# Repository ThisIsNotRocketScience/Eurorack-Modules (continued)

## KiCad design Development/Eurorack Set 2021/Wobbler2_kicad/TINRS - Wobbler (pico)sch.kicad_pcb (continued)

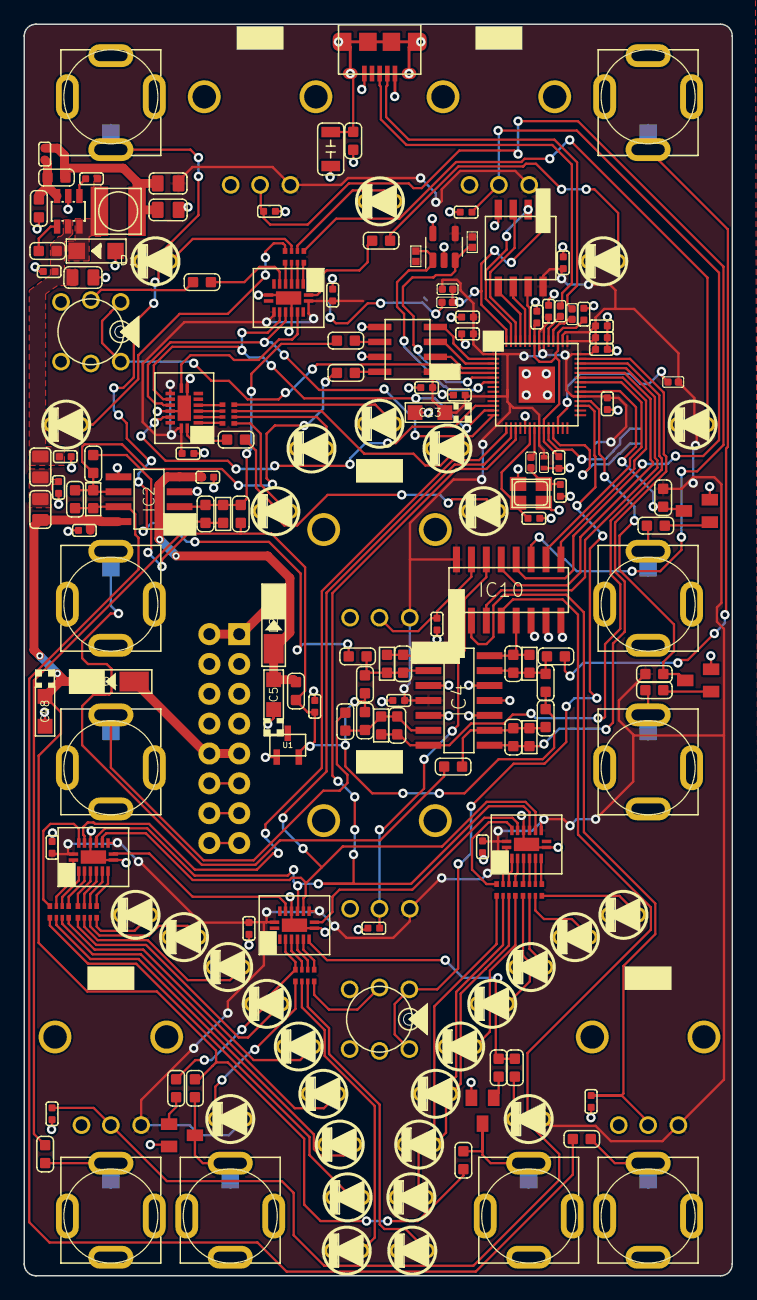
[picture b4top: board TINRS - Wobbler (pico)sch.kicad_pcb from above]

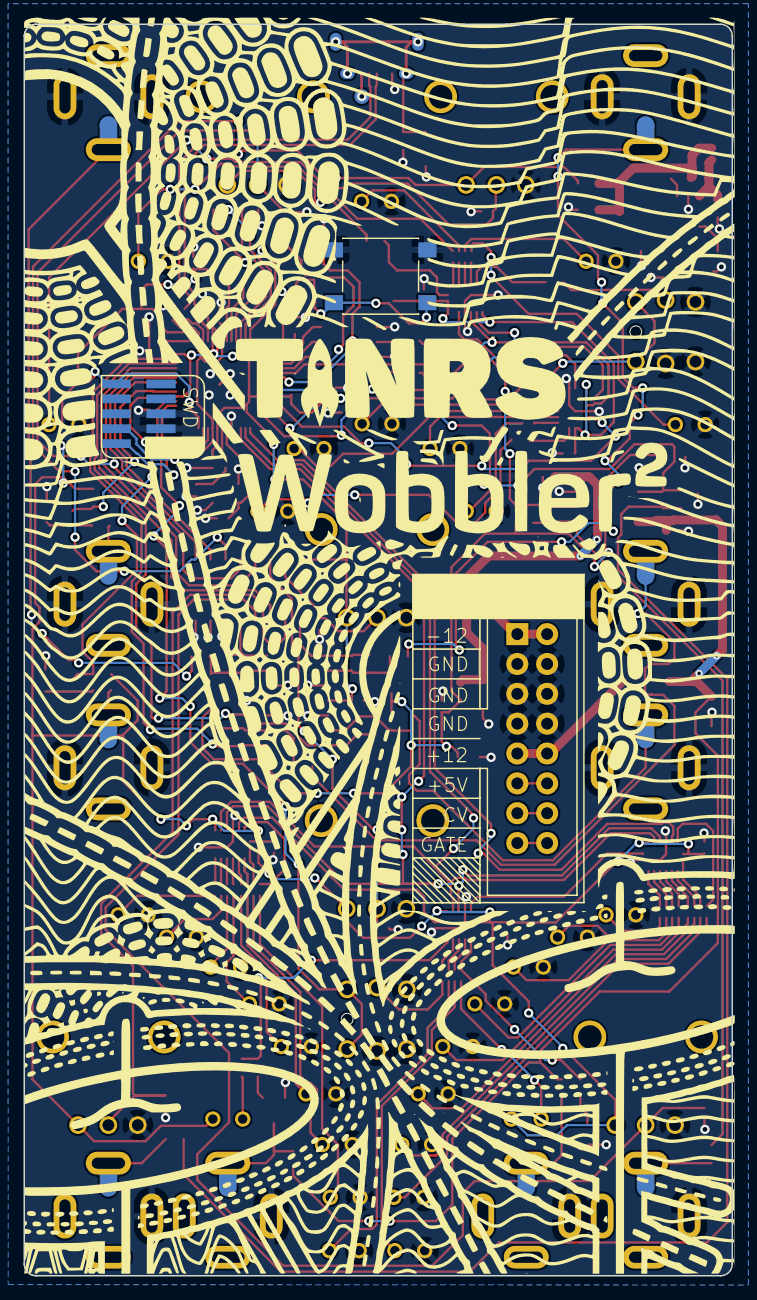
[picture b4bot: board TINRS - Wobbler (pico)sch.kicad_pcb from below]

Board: 2 copper layers, 60.3 x 106.5 mm, 181 parts (5 on the bottom side), 157 nets.

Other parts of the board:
A1: Wobbler2_PCBArt; Wobbler2_art
R35, R38: 2k; R0402
U2: AT24CS01-STUM; SOT-23-5

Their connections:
/MCU & Eeprom/EEPROM_SCL: R38.2, U2.1 (SCL); also elsewhere on the board
/MCU & Eeprom/EEPROM_SDA: R35.1, U2.3 (SDA); also elsewhere on the board
GND: U2.2 (GND), U2.5 (WP); also elsewhere on the board

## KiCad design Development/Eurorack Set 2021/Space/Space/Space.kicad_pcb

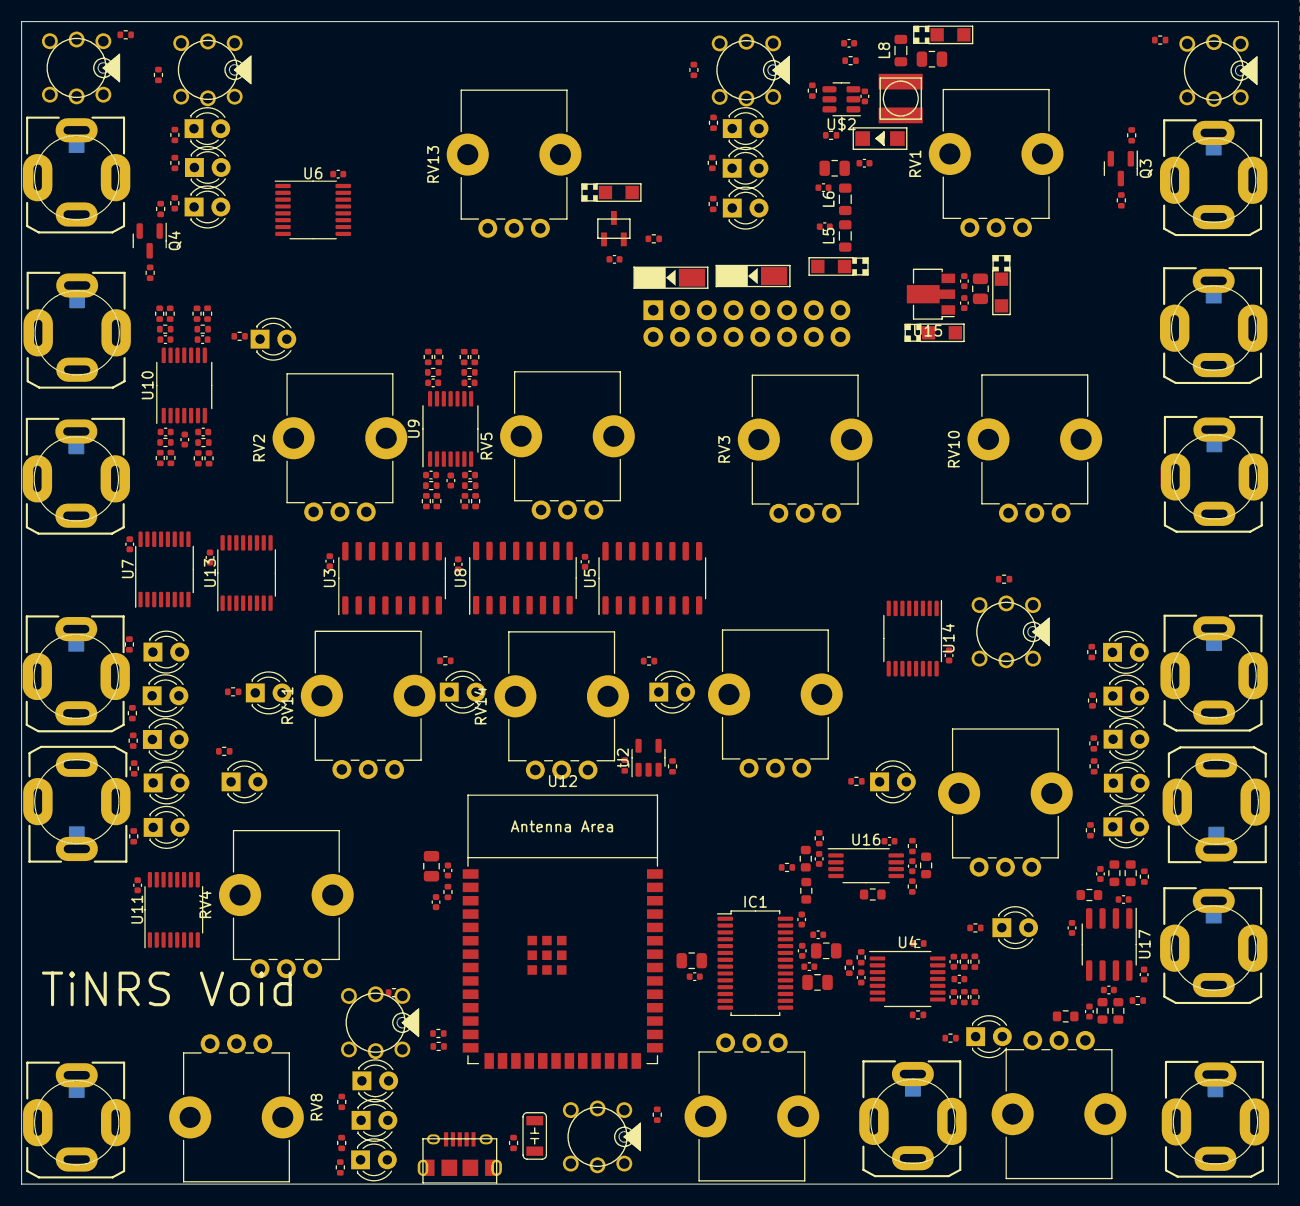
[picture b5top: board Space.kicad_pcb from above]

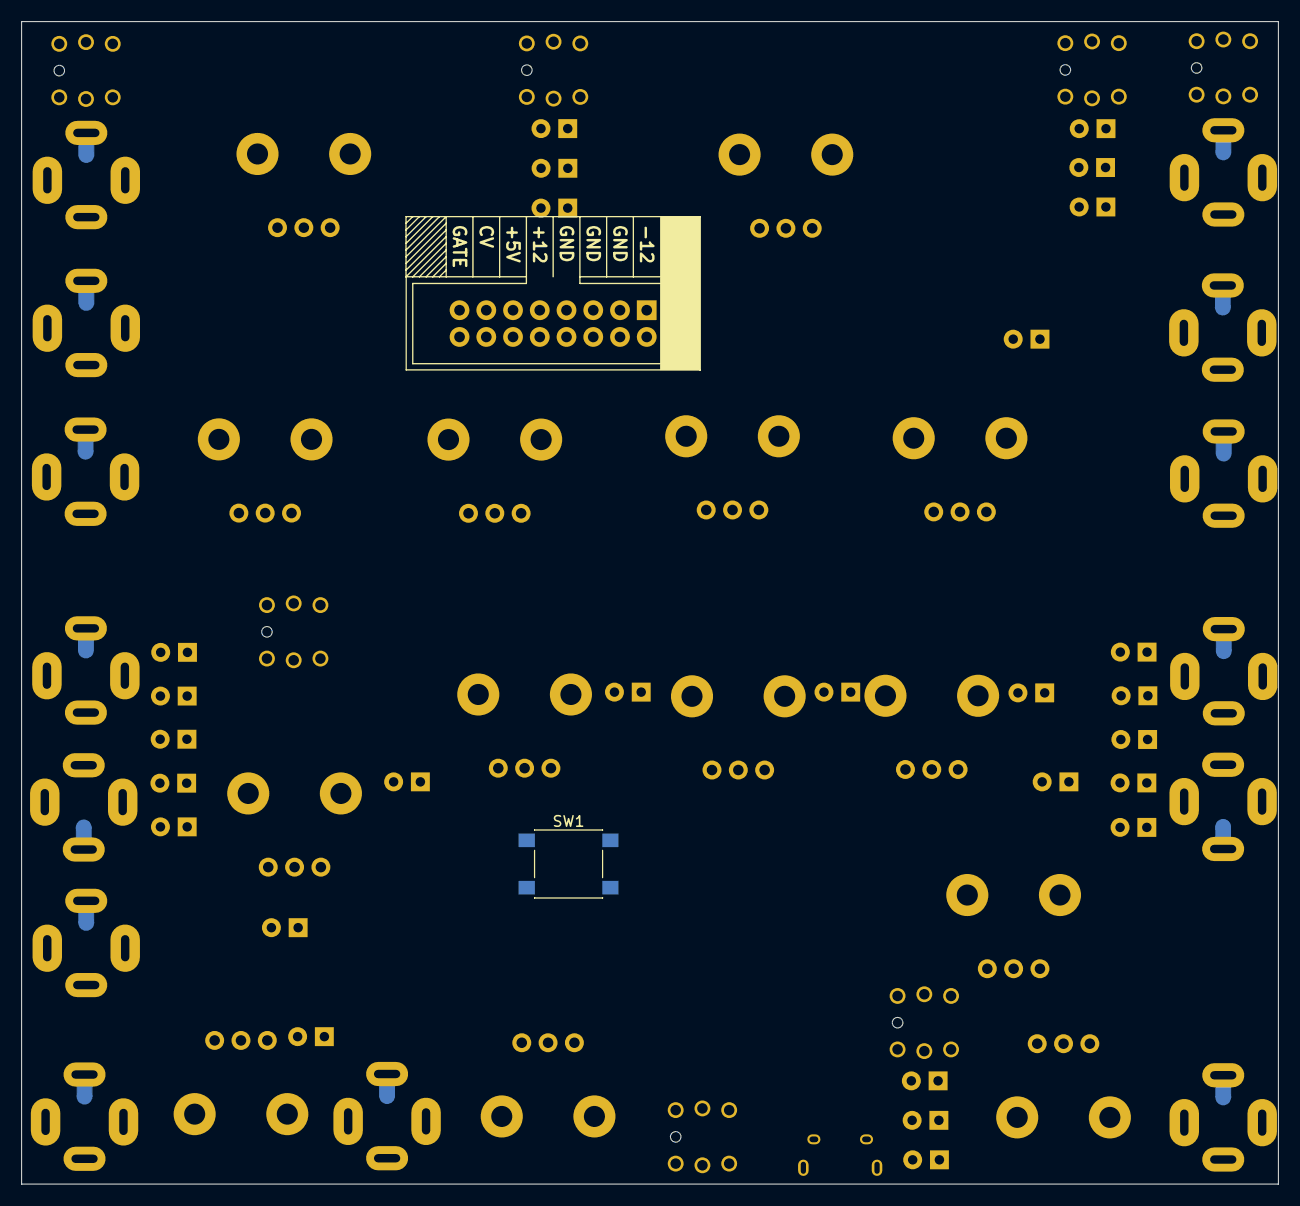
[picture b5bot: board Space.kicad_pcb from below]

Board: 2 copper layers, 119.4 x 110.4 mm, 248 parts (2 on the bottom side), 189 nets, no tracks yet.

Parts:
C1, C2, C48, C51, C52, C53, C56: 1759017; C_0402_1005Metric
C3, C8, C50, C55, C58: 197427; CASE-A_3216
C7, C54, C61: 22u; C_0805_2012Metric
C9, C12, C15: 10u; C_0805_2012Metric
C10, C13, C16, C26, C27, C28, C29, C31, C32, C33, C34, C35, C36, C45, C46, C47, C62, C63, C64: 100n; C_0402_1005Metric
C11, C14: 2.2n; C_0402_1005Metric
C24, C25: 470p; C_0402_1005Metric
C37, C38, C39, C40, C41, C42, C43, C44: 3.3n; C_0402_1005Metric
C49: 10uF; C_0805_2012Metric
C57: 1301804; C_0402_1005Metric
C59: 4.7n 100v; C3216
C60: 1u; C_0402_1005Metric
C65, C66: 100p; C_0402_1005Metric
C67, C68, C69, C70: 47p; C_0402_1005Metric
D1, D4, D7, D8, D9, D10, D11, D12, D13, D14, D15, D16, D17, D18, D19, D20, D23, D24, D25, D26, D27, D28, D29, D30, D31, D32, D33: LED; LED_D3.0mm_FlatTop
D3: D-SOD-123; SOD123
D21, D22: D-SMA; DO-214AC
IC1: PCM3060; TSSOP-28_4.4x9.7mm_P0.65mm
J1: unknown; POWER_16_SHROUDED
J14: MICRO-USB-5P; C132563
JACK1, JACK2, JACK3, JACK4, JACK5, JACK6, JACK7, JACK8, JACK9, JACK10, JACK11, JACK12, JACK13, JACK14: AUDIO-JACK_SMALLSYMBOLNODRILL; 3.5MM-JACK-SWITCH-13MM-NOHOLES-TESTPAD
L5, L6, L8: 0.1uH C76737; L_0805_2012Metric
L7: 4.7uH; L0420
Q3, Q4: MMBT3904; SOT-23
R1, R2, R4, R25, R26, R27, R28, R29, R30, R31, R32, R33, R34, R35, R36, R37, R62, R63, R64, R65, R79, R80, R81, R82, R83, R84, R85, R86, R87, R88, R89, R90, R91, R92, R110, R115: 56; R_0402_1005Metric
R38, R39, R40, R41, R44, R45, R46, R47, R50, R51, R52, R53, R56, R57, R58, R59, R67, R99, R102, R103, R104, R105, R106, R114, R116, R117: 100k; R_0402_1005Metric
R42, R43, R48, R49, R54, R55, R60, R61: 33k; R_0402_1005Metric
R66, R68, R100, R101: 12.1k; R_0603_1608Metric
R69, R70, R71, R72, R93, R94, R95, R96: unknown; R_0402_1005Metric
R73, R74: 0; R_0402_1005Metric
R75: 1M; R_0402_1005Metric
R76, R77: 2k; R_0402_1005Metric
R78: 10k; R_0402_1005Metric
R97, R98: 100; R_0402_1005Metric
R107, R112: 4.42k; R_0603_1608Metric
R108, R113: 4.02k; R_0603_1608Metric
R109, R111: 37.5k; R_0603_1608Metric
RV1, RV2, RV3, RV4, RV5, RV6, RV8, RV9, RV10, RV11, RV13, RV14, RV15, RV16: R_Potentiometer; Potentiometer_Alps_RK09K_Single_Vertical
SW1: SW_Push; SW_Push_1P1T_NO_6x6mm_H9.5mm
U1: 9778330; SOT95P237X112-3N
U2: AT24CS01-STUM; SOT-23-5
U3, U5, U8: 4052; SO-16_3.9x9.9mm_P1.27mm
U4: TL074; TSSOP-14_4.4x5mm_P0.65mm
U6, U7, U11, U13, U14: 74HC595; TSSOP-16_4.4x5mm_P0.65mm
U9, U10: MCP6004; TSSOP-14_4.4x5mm_P0.65mm
U12: ESP32-S3-WROOM-1
U15: HT7550-1; SOT-89-3
U16: MCP6022; TSSOP-8_4.4x3mm_P0.65mm
U17: NE5532; SOIC-8_3.9x4.9mm_P1.27mm
U$2: BL9342; SOT-23-6
U$3, U$4, U$5, U$6, U$7, U$8, U$9: SWITCH_W_LED_PB6149L-X-102YELLOW; PB6149L

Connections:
+3V3: C9.1, C10.1, C31.1, C32.1, C33.1, C34.1, C35.1, C36.1, C45.2, C46.1, C55.+ (1), C61.1, C62.1, C63.1, C64.1, IC1.7 (VDD), L8.2, R76.2, R77.1, R78.1, R93.2, R95.2, RV1.3, RV2.3, RV3.3, RV4.3, RV5.3, RV6.3, RV8.3, RV9.3, RV10.3, RV11.3, RV13.3, RV14.3, RV15.3, RV16.3, U2.4 (VCC), U3.16 (VDD), U5.16 (VDD), U6.10 (~SRCLR), U6.16 (VCC), U7.10 (~SRCLR), U7.16 (VCC), U8.16 (VDD), U9.4 (V+), U10.4 (V+), U11.10 (~SRCLR), U11.16 (VCC), U12.2 (3V3), U13.10 (~SRCLR), U13.16 (VCC), U14.10 (~SRCLR), U14.16 (VCC)
+5V: C1.1, C7.2, C8.+ (1), C15.1, C16.1, C47.1, IC1.24 (VCC), U15.3 (OUT), U16.8 (V+)
+12V: C2.1, C3.+ (1), C27.1, C28.1, C50.+ (1), D21.2 (-), L5.1, U4.4 (V+), U15.2 (IN), U17.8 (V+)
-5V: C57.2, R38.1, R40.1, R44.1, R46.1, R50.1, R52.1, R56.1, R58.1, R72.2, U1.2 (ANODE)
-12V: C26.1, C29.1, C58.- (2), D22.1 (+), R72.1, U4.11 (V-), U17.4 (V-)
/BOOTSEL_BUT: SW1.2, U12.27 (GPIO0/BOOT)
/BUTTON_DELAY: U12.29 (SPIIO7/GPIO36/FSPICLK/SUBSPICLK), U$7.1, U$7.2
/BUTTON_FREEZE: U12.23 (GPIO21), U$4.1, U$4.2
/BUTTON_PITCH: U12.24 (GPIO47/SPICLK_P/SUBSPICLK_P_DIFF), U$8.1, U$8.2
/BUTTON_PITCHPOINT: U12.25 (GPIO48/SPICLK_N/SUBSPICLK_N_DIFF), U$5.1, U$5.2
/BUTTON_SEND: U12.16 (GPIO46), U$6.1, U$6.2
/BUTTON_TAIL: U12.26 (GPIO45), U$9.1, U$9.2
/BUTTON_TAP: U12.28 (SPIIO6/GPIO35/FSPID/SUBSPID), U$3.1, U$3.2
/CODEC_SCL: IC1.1 (MC/SCL/FMT), U12.15 (GPIO3/TOUCH3/ADC1_CH2)
/CODEC_SDA: IC1.2 (MD/SDA/DEMP), U12.38 (GPIO2/TOUCH2/ADC1_CH1)
/CVADC0: U8.13 (X), U12.19 (GPIO11/TOUCH11/ADC2_CH0/FSPID/FSPIIO5/S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)
/CVADC1: U8.3 (Y), U12.20 (GPIO12/TOUCH12/ADC2_CH1/FSPICLK/FSPIIO6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)
/CVJacks/CV_DELAY_FEEDBACK: JACK2.TIP, R41.1
/CVJacks/CV_DELAY_LENGTH: JACK1.TIP, R39.1
/CVJacks/CV_MIX: JACK7.TIP, R57.1
/CVJacks/CV_PITCH_CONTROL: JACK4.TIP, R47.1
/CVJacks/CV_PITCH_TRANSPOSE: JACK3.TIP, R45.1
/CVJacks/CV_TAIL_LENGTH: JACK6.TIP, R53.1
/CVJacks/CV_TAIL_TEMPERATURE: JACK5.TIP, R51.1
/CVJacks/JACK_FREEZE: JACK9.TIP, R96.1
/CVJacks/JACK_TAP: JACK10.TIP, R94.1
/CVJacks/XCV0: C38.2, R43.2, U8.12 (X0), U9.1
/CVJacks/XCV1: C40.2, R49.2, U8.14 (X1), U9.7
/CVJacks/XCV2: C42.2, R55.2, U8.15 (X2), U9.8
/CVJacks/XCV3: C44.2, R61.2, U8.11 (X3), U9.14
/CVJacks/XCV4: C37.2, R42.2, U8.1 (Y0), U10.1
/CVJacks/XCV5: C39.2, R48.2, U8.5 (Y1), U10.7
/CVJacks/XCV6: C41.2, R54.2, U8.2 (Y2), U10.8
/CVJacks/XCV7: C43.2, R60.2, U8.4 (Y3), U10.14
/CVMUX0: U3.10 (A), U5.10 (A), U8.10 (A), U12.30 (SPIDQS/GPIO37/FSPIQ/SUBSPIQ)
/CVMUX1: U3.9 (B), U5.9 (B), U8.9 (B), U12.31 (GPIO38/FSPIWP/SUBSPIWP)
/CodecBuffer/BIAS_BUFFERED: R102.1, U4.6 (-), U4.7
/CodecBuffer/BIAS_INVERTED: R68.1, R100.1, R103.2, R106.1, R117.1, U4.1
/CodecBuffer/In_Jack_Left: JACK13.TIP, JACK14.SWITCH, R67.1
/CodecBuffer/In_Jack_Right: JACK14.TIP, R99.1
/CodecBuffer/Out_Jack_Left: JACK11.TIP, R110.2
/CodecBuffer/Out_Jack_Right: JACK12.TIP, R115.2
/CodecBuffer/Out_Left: IC1.20 (VOUTL+), R114.1
/CodecBuffer/Out_Right: IC1.18 (VOUTR+), R105.1
/EEPROM_SCL: R77.2, U2.1 (SCL), U12.33 (MTDO/GPIO40/CLK_OUT2)
/EEPROM_SDA: R76.1, U2.3 (SDA), U12.32 (MTCK/GPIO39/CLK_OUT3/SUBSPICS1)
/EN: C60.1, R78.2, U12.3 (EN)
/I2S_BCLK: IC1.5 (BCK1), U12.11 (GPIO18/U1RXD/ADC2_CH7/CLK_OUT3)
/I2S_LRC: IC1.4 (LRCK1), U12.10 (GPIO17/U1TXD/ADC2_CH6)
/JACK_FREEZE: Q3.3 (C), R95.1, U12.39 (GPIO1/TOUCH1/ADC1_CH0)
/JACK_TAP: Q4.3 (C), R93.1, U12.34 (MTDI/GPIO41/CLK_OUT1)
/KNOBADC0: U3.13 (X), U12.7 (GPIO7/TOUCH7/ADC1_CH6)
/KNOBADC1: U3.3 (Y), U12.12 (GPIO8/TOUCH8/ADC1_CH7/SUBSPICS1)
/KNOBADC2: U5.13 (X), U12.17 (GPIO9/TOUCH9/ADC1_CH8/FSPIHD/SUBSPIHD)
/KNOBADC3: U5.3 (Y), U12.18 (GPIO10/TOUCH10/ADC1_CH9/FSPICS0/FSPIIO4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)
/Knobs/KNOB_DELAY: RV14.2, U3.1 (Y0)
/Knobs/KNOB_DELAY_FEEDBACK: RV2.2, U3.14 (X1)
/Knobs/KNOB_DELAY_LENGTH: RV13.2, U3.12 (X0)
/Knobs/KNOB_DELAY_PATTERN: RV5.2, U3.15 (X2)
/Knobs/KNOB_DIFFUSE: RV11.2, U3.11 (X3)
/Knobs/KNOB_DIFFUSE_STYLE: RV4.2, U3.5 (Y1)
/Knobs/KNOB_ENVTRACK: RV9.2, U5.5 (Y1)
/Knobs/KNOB_MAIN: RV15.2, U5.1 (Y0)
/Knobs/KNOB_PITCH_CONTROL: RV16.2, U5.2 (Y2)
/Knobs/KNOB_PITCH_TRANSPOSE: RV8.2, U3.2 (Y2)
/Knobs/KNOB_TAIL: RV6.2, U5.11 (X3)
/Knobs/KNOB_TAIL_CHORALITY: RV3.2, U5.15 (X2)
/Knobs/KNOB_TAIL_LENGTH: RV1.2, U5.12 (X0)
/Knobs/KNOB_TAIL_TEMPERATURE: RV10.2, U5.14 (X1)
/LEDCLK: U6.11 (SRCLK), U7.11 (SRCLK), U11.11 (SRCLK), U12.4 (GPIO4/TOUCH4/ADC1_CH3), U13.11 (SRCLK), U14.11 (SRCLK)
/LEDDAT: U6.14 (SER), U12.6 (GPIO6/TOUCH6/ADC1_CH5)
/LEDLAT: U6.12 (RCLK), U7.12 (RCLK), U11.12 (RCLK), U12.5 (GPIO5/TOUCH5/ADC1_CH4), U13.12 (RCLK), U14.12 (RCLK)
/LED_DELAY: R85.1, U6.3 (QD)
/LED_DELAYMODE_1: D26.2 (A), U6.15 (QA)
/LED_DELAYMODE_2: D27.2 (A), U6.1 (QB)
/LED_DELAYMODE_3: D28.2 (A), U6.2 (QC)
/LED_ENVTRACKER_OUT: D1.2 (A), U11.1 (QB)
/LED_FREEZE: R62.1, U7.15 (QA)
/LED_PITCH: R86.1, U11.7 (QH)
/LED_PITCHMODE_1: D23.2 (A), U11.4 (QE)
/LED_PITCHMODE_2: D24.2 (A), U11.5 (QF)
/LED_PITCHMODE_3: D25.2 (A), U11.6 (QG)
/LED_PITCHPOINT: R63.1, U11.3 (QD)
/LED_PP_DELAY: D15.2 (A), U7.6 (QG)
/LED_PP_DELAY_FEEDBACK: D13.2 (A), U7.5 (QF)
/LED_PP_DIFFUSE: D11.2 (A), U7.4 (QE)
/LED_PP_DRY: D7.2 (A), U7.2 (QC)
/LED_PP_MAINPOST: D17.2 (A), U7.7 (QH)
/LED_PP_MAINPRE: D9.2 (A), U7.3 (QD)
/LED_PP_TAIL: D19.2 (A), U11.15 (QA)
/LED_SEND: R81.1, U11.2 (QC)
/LED_TAIL: R90.1, U6.7 (QH)
/LED_TAILMODE_1: D29.2 (A), U6.4 (QE)
/LED_TAILMODE_2: D30.2 (A), U6.5 (QF)
/LED_TAILMODE_3: D31.2 (A), U6.6 (QG)
/LED_TAP: R79.1, U7.1 (QB)
/LED_VU_IN_1: D16.2 (A), U13.15 (QA)
/LED_VU_IN_2: D18.2 (A), U13.1 (QB)
/LED_VU_IN_3: D20.2 (A), U13.2 (QC)
/LED_VU_IN_4: D32.2 (A), U13.3 (QD)
/LED_VU_IN_5: D33.2 (A), U13.4 (QE)
/LED_VU_OUT_1: D4.2 (A), U14.15 (QA)
/LED_VU_OUT_2: D8.2 (A), U14.1 (QB)
/LED_VU_OUT_3: D10.2 (A), U14.2 (QC)
/LED_VU_OUT_4: D12.2 (A), U14.3 (QD)
/LED_VU_OUT_5: D14.2 (A), U14.4 (QE)
/MCLK: IC1.6 (SCKI1), U12.9 (GPIO16/U0CTS/ADC2_CH5/XTAL_32K_NH5)
/MODENV_PWM: JACK8.TIP, U12.35 (MTMS/GPIO42)
/PCM3060/VCOM: C12.1, C13.1, IC1.21 (VCOM), U4.5 (+)
/PCM3060/VINL: C14.2, IC1.25 (VINL), R97.2
/PCM3060/VINR: C11.2, IC1.26 (VINR), R98.2
/Power/3.3v_regulator_feedback_1: C54.2, C56.1, L7.2, L8.1, R70.1
/Power/3.3v_regulator_feedback_2: C56.2, R70.2, R71.1, U$2.3 (FB)
/Power/3.3v_regulator_filter: C51.2, L5.2, L6.1
/Power/3.3v_regulator_inputside: C49.2, C52.2, C53.2, L6.2, R69.2, U$2.5 (VIN)
/Power/3.3v_regulator_switchoutput: C48.1, D3.-, L7.1, U$2.6 (SW)
/Power/min12in: D22.2 (-), J1.1 (-12V), J1.2 (-12V)
/Power/plus12in: D21.1 (+), J1.9 (+12V), J1.10 (+12V)
/USB_N: J14.2 (DM), R74.1
/USB_P: J14.3 (DP), R73.1
GND: C1.2, C2.2, C3.- (2), C7.1, C8.- (2), C9.2, C10.2, C11.1, C12.2, C13.2, C14.1, C15.2, C16.2, C24.1, C25.1, C26.2, C27.2, C28.2, C29.2, C31.2, C32.2, C33.2, C34.2, C35.2, C36.2, C45.1, C46.2, C47.2, C49.1, C50.- (2), C51.1, C52.1, C53.1, C54.1, C55.- (2), C57.1, C58.+ (1), C59.1, C60.2, C61.2, C62.2, C63.2, C64.2, D3.+, IC1.8 (DGND), IC1.9 (SCKI2), IC1.10 (BCK2), IC1.11 (LRCK2), IC1.16 (SGND), IC1.22 (AGND2), IC1.23 (AGND1), IC1.27 (~MS~/ADR/IFMD), IC1.28 (MODE), J1.3 (GND), J1.4 (GND), J1.5 (GND), J1.6 (GND), J1.7 (GND), J1.8 (GND), J14.5 (GND@1), JACK1.RING, JACK1.SWITCH, JACK2.RING, JACK2.SWITCH, JACK3.RING, JACK3.SWITCH, JACK4.RING, JACK4.SWITCH, JACK5.RING, JACK5.SWITCH, JACK6.RING, JACK6.SWITCH, JACK7.RING, JACK7.SWITCH, JACK8.RING, JACK9.RING, JACK9.SWITCH, JACK10.RING, JACK10.SWITCH, JACK11.RING, JACK12.RING, JACK13.RING, JACK13.SWITCH, JACK14.RING, Q3.2 (E), Q4.2 (E), R1.2, R2.2, R4.2, R25.2, R26.2, R27.2, R28.2, R29.2, R30.2, R31.2, R32.2, R33.2, R34.2, R35.2, R36.2, R37.2, R64.2, R65.2, R71.2, R75.1, R80.2, R82.2, R83.2, R84.2, R87.2, R88.2, R89.2, R91.2, R92.2, RV1.1, RV2.1, RV3.1, RV4.1, RV5.1, RV6.1, RV8.1, RV9.1, RV10.1, RV11.1, RV13.1, RV14.1, RV15.1, RV16.1, SW1.1, U1.1 (CATHODE), U2.2 (GND), U2.5 (WP), U3.4 (Y3), U3.6 (Inh), U3.7 (VEE), U3.8 (VSS), U4.3 (+), U4.10 (+), U4.12 (+), U5.4 (Y3), U5.6 (Inh), U5.7 (VEE), U5.8 (VSS), U6.8 (GND), U6.13 (~OE), U7.8 (GND), U7.13 (~OE), U8.6 (Inh), U8.7 (VEE), U8.8 (VSS), U9.3 (+), U9.5 (+), U9.10 (+), U9.11 (V-), U9.12 (+), U10.3 (+), U10.5 (+), U10.10 (+), U10.11 (V-), U10.12 (+), U11.8 (GND), U11.13 (~OE), U12.1 (GND), U12.40 (GND), U12.41 (GND), U13.8 (GND), U13.13 (~OE), U14.8 (GND), U14.13 (~OE), U15.1 (GND), U16.3 (+), U16.4 (V-), U16.5 (+), U17.3 (+), U17.5 (+), U$2.2 (GND), U$3.3, U$3.4, U$3.LEDNEG (NEG), U$4.3, U$4.4, U$4.LEDNEG (NEG), U$5.3, U$5.4, U$5.LEDNEG (NEG), U$6.3, U$6.4, U$6.LEDNEG (NEG), U$7.3, U$7.4, U$7.LEDNEG (NEG), U$8.3, U$8.4, U$8.LEDNEG (NEG), U$9.3, U$9.4, U$9.LEDNEG (NEG)
unnamed: C24.2, R107.2, R108.1, R109.1
unnamed: C25.2, R111.1, R112.2, R113.1
unnamed: C65.1, R66.2, R97.1, U16.1
unnamed: C66.1, R98.1, R101.2, U16.7
unnamed: C67.1, R104.2, R112.1, U4.8
unnamed: C68.1, R109.2, R110.1, U17.1
unnamed: C69.1, R111.2, R115.1, U17.7
unnamed: C70.1, R107.1, R116.2, U4.14
unnamed: D1.1 (K), R1.1
unnamed: D4.1 (K), R2.1
unnamed: D7.1 (K), R4.1
unnamed: D8.1 (K), R25.1
unnamed: D9.1 (K), R26.1
unnamed: D10.1 (K), R27.1
unnamed: D11.1 (K), R28.1
unnamed: D12.1 (K), R29.1
unnamed: D13.1 (K), R30.1
unnamed: D14.1 (K), R31.1
unnamed: D15.1 (K), R32.1
unnamed: D16.1 (K), R33.1
unnamed: D17.1 (K), R34.1
unnamed: D18.1 (K), R35.1
unnamed: D19.1 (K), R36.1
unnamed: D20.1 (K), R37.1
unnamed: D23.1 (K), R64.1
unnamed: D24.1 (K), R65.1
unnamed: D25.1 (K), R80.1
unnamed: D26.1 (K), R82.1
unnamed: D27.1 (K), R83.1
unnamed: D28.1 (K), R84.1
unnamed: D29.1 (K), R87.1
unnamed: D30.1 (K), R88.1
unnamed: D31.1 (K), R89.1
unnamed: D32.1 (K), R91.1
unnamed: D33.1 (K), R92.1
unnamed: C59.2, J14.B@2 (GND@2), J14.B@4 (GND@2), J14.B@5 (GND@2), J14.B@6 (GND@3), J14.B@7 (GND@2), J14.B@8 (GND@2), J14.B@9 (GND@2), J14.B@12 (GND@2), R75.2
unnamed: Q3.1 (B), R96.2
unnamed: Q4.1 (B), R94.2
unnamed: R102.2, R103.1, U4.2 (-)
unnamed: C67.2, R104.1, R105.2, R106.2, U4.9 (-)
unnamed: C70.2, R114.2, R116.1, R117.2, U4.13 (-)
unnamed: U6.9 (QH'), U7.14 (SER)
unnamed: C38.1, R40.2, R41.2, R43.1, U9.2 (-)
unnamed: C40.1, R46.2, R47.2, R49.1, U9.6 (-)
unnamed: C42.1, R52.2, R53.2, R55.1, U9.9 (-)
unnamed: C44.1, R58.2, R59.2, R61.1, U9.13 (-)
unnamed: C37.1, R38.2, R39.2, R42.1, U10.2 (-)
unnamed: C39.1, R44.2, R45.2, R48.1, U10.6 (-)
unnamed: C41.1, R50.2, R51.2, R54.1, U10.9 (-)
unnamed: C43.1, R56.2, R57.2, R60.1, U10.13 (-)
unnamed: U11.9 (QH'), U13.14 (SER)
unnamed: U7.9 (QH'), U11.14 (SER)
unnamed: R74.2, U12.13 (GPIO19/U1RTS/ADC2_CH8/CLK_OUT2/USB_D-)
unnamed: R73.2, U12.14 (GPIO20/U1CTS/ADC2_CH9/CLK_OUT1/USB_D+)
unnamed: U13.9 (QH'), U14.14 (SER)
unnamed: C65.2, R66.1, R67.2, R68.2, U16.2 (-)
unnamed: C66.2, R99.2, R100.2, R101.1, U16.6 (-)
unnamed: C68.2, R108.2, U17.2 (-)
unnamed: C69.2, R113.2, U17.6 (-)
unnamed: C48.2, U$2.1 (BST)
unnamed: R69.1, U$2.4 (EN)
unnamed: R79.2, U$3.LEDPOS (POS)
unnamed: R62.2, U$4.LEDPOS (POS)
unnamed: R63.2, U$5.LEDPOS (POS)
unnamed: R81.2, U$6.LEDPOS (POS)
unnamed: R85.2, U$7.LEDPOS (POS)
unnamed: R86.2, U$8.LEDPOS (POS)
unnamed: R90.2, U$9.LEDPOS (POS)

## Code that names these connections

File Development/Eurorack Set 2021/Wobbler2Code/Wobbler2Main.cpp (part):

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#define DAC_CS 1
#define DAC_DAT 2

#define FASTMODE_BUT 5

#define SR_2_DAT 9
#define SR_2_CLK 10
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#define SR_1_CLK 13
#define SR_1_LATCH 14

#define RESET_PATTERN_BUT 20
#define RESET_PATTERN 21
#define SYNC_LFO 22
#define MUX_A 24
#define MUX_B 25

#define ADC_MUX0 ADC0
#define ADC_MUX1 ADC1
#define ADC_FREQ ADC2
#define ADC_SHAPE ADC3

uint16_t COMBINE(int32_t A, int32_t B)
{
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    return (uint16_t)R;
}

#define KNOB_MOD muxed[0][0]
#define KNOB_FREQ muxed[0][1]
#define KNOB_SHAPE muxed[0][2]
#define KNOB_PHASE muxed[0][3]

#define ADC_PHASE muxed[1][0]
#define ADC_MOD muxed[1][1]
#define KNOB_PHASED muxed[1][2]
#define KNOB_NORMAL muxed[1][3]
#include "Wobbler2.h"
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        gpio_put(clk, 1);
        gpio_put(clk, 0);
    }
    gpio_put(latch, 1);
    gpio_put(latch, 0);
}

uint8_t pwm = 0;
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    Wobbler2_Init(&TheWobbler);
    int curmux = 0;

    gpio_init(RESET_PATTERN_BUT);
    gpio_dir(RESET_PATTERN_BUT, GPIO_IN);
    gpio_pull_up(RESET_PATTERN_BUT);

    gpio_init(RESET_PATTERN);
    gpio_dir(RESET_PATTERN, GPIO_IN);
    gpio_pull_up(RESET_PATTERN);

    gpio_init(FASTMODE_BUT);
    gpio_dir(FASTMODE_BUT, GPIO_IN);
    gpio_pull_up(FASTMODE_BUT);
    gpio_init(MUX_A);
    gpio_dir(MUX_A, GPIO_OUT);
    gpio_init(MUX_B);
    gpio_dir(MUX_B, GPIO_OUT);

    gpio_init(DAC_CS);
    gpio_dir(DAC_CS, GPIO_OUT);
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
        curmux = (curmux + 1) % 4;
        if ((curmux & 1) == 1)
            gpio_put(MUX_A, 1);
        else
            gpio_put(MUX_A, 0);
        if ((curmux & 2) == 2)
            gpio_put(MUX_B, 1);
        else
            gpio_put(MUX_B, 0);
        adc_input_select(0);
        muxed[0][curmux] = adc_read() * 16;
        adc_input_select(1);
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
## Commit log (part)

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2015-10-31 Initial commit - boards in a terrible state so far
    Tadaaa
2015-10-31 Parts libs for euroracks
2015-10-31 Power on the multiples board
2015-11-01 K22 baseboard part outline
2015-11-01 Updated input/output jacks
2015-11-03 Goldfish Frontpanel Progress + eurolib extensions
2015-11-04 ScaleOffset board nearing readiness
2015-11-04 Updated europarts library in all boards.
2015-11-05 Redone most of the goldfish front cv summing, added opamps to library
2015-11-05 Fixed up scaleoffset module. Added cv and gate outputs
2015-11-05 GateRhythm added
2015-11-05 GateRhythm cleanup + decoupling + routing.
2015-11-05 LogicThingie - extra button, no serial, better routing
2015-11-05 Routing updates and ScaleOffset to 6hp
2015-11-05 Cleaning up folder
2015-11-05 Goldfish update by Lauri - ScaleOffset fix
2015-11-05 Lots of board updates
2015-11-05 Fix K22 baseboard pinout
2015-11-06 Buffered Multipes Spacepacked
2015-11-06 TestBench - initial commit
2015-11-06 Added inverted silk for 10pin power - added opamps for leds
2015-11-06 DRC & ERC on all boards = green now.
2015-11-06 Added holes to the panel layer to create complete lasercutter dxf exports possible
2015-11-09 Renamed LogicThingie to SonicScrewdriver - cosmetic changes, panel exports, cam folders
2015-11-09 Opamp Devboard added
2015-11-11 Added LauriFilter MCUfront - updated opamp board with formulas
2015-11-11 TimeLord board + minor gaterhythm update
2015-11-11 LauriFilter has switches + 595 for leds
2015-11-11 Many many changes after crosschecking by Lauri
2015-11-13 TimeLord update
2015-11-17 pre order fixes
2015-11-17 Pre-order fixes
2015-11-19 eurorack prototyping board added
2015-11-19 updated protoboard with better attiny area
2015-11-19 repo cleanup
2015-11-19 frontpanel designs
2015-11-19 more repo cleaning + Readme
2015-11-19 DipTrace files for the codec and power supply.
2015-11-23 small cosmetic changes- reversed the led polarity
2015-12-02 BodgeFix 1 : multiples leds swapped + noted the inversion
2015-12-02 Bodge 2 - different led viz schematic for scaleoffset
2015-12-02 More bodges... different led setup for scaleoffset, gaterhythm still has buttons reversed
2015-12-03 GateRhythm updates - updated switch pattern in zephodlibrary (not in this repo)
2015-12-04 More bodgefixes + led reversals
2015-12-05 More bodges - -12v line on fishfront, leds reversal, protection resistors on sonicscrewdriver
2015-12-13 Codec pcb rev2.
2015-12-18 Shifted codecboard power connector by 50 mil.
2015-12-24 Changed drill radius for potentiometer in library
2016-01-18 Fiducials!
2016-01-19 Updated library shape for jacks - updated all boards to match
2016-01-27 Library updated for MCUBoard, many tweaks.
2016-01-30 LEDDistortion converted to board
2016-01-30 panel dxfs and LEDDistortion updates
2016-01-30 More lauri feedback incorporated
2016-01-30 Optional LR Phasor + serial switch jumper on LED distortion
2016-01-31 Full configurable LRC stage on the LEDDistortion - placement cleanup
2016-02-02 New busboard
2016-08-04 Finally some updates...
2016-08-25 ScrewDriver fixes - codecboard for series 2 added - passthrough board - melody initial
2016-08-26 Melody And Screwdriver Updates
2016-08-29 Melody progress
2016-08-30 Melody Updates
2016-09-01 Added Simple Switch Module - Added DESC attribute for some input elements
2016-09-05 added router settings, Melody polishing
2016-09-07 Clearance updates - removed double clocktrace
2016-09-10 4io frontpanel, trigger thinner
2016-09-15 Final tweaks for the order - initial bom update for tuesday
2016-09-29 eeprom pinout update
2016-09-30 Fixes to the BOM
2016-10-03 Tuesday r2 handrouted & panel details
2016-10-06 SMT-led version of the Tuesday Module
2016-10-10 Tuesday schematic updates for SMT led version, dxf for panel, gerber package
2016-10-18 Envelope Initital Commit
2016-10-24 Envelope Commit
2016-10-24 Wasp concept.. not sure about this
2016-11-07 Envelope Board and Schematic detail fixes
2016-11-10 Envelope Routing Progress
2016-11-10 Envelope Handrouting progress
2016-11-10 Envelope Board Routed
2016-11-10 More routing
2016-11-10 VCA board
2016-11-10 CodecThing and DelayFront
2016-11-10 Envelope Routing Optimizing
2016-11-11 VCA Rerouting
2016-11-11 Forgot to power one opamp.. whoops
2016-11-11 Cleanup
2016-11-12 VCA updates
2016-11-15 Frontpanel DXFs, VCA update, CVSummer fixes
2016-11-15 Summer and Envelope updates (leftover opamp wiring)
2016-11-24 Minor wasp tweaks.. nowhere near completion
2016-11-26 Many routing & artwork updates
2016-11-28 Some extra patterns
2016-11-30 Tiny routing updte
2016-12-02 Doublechecks & artwork prep
2016-12-03 Keychan and logos
2016-12-25 First Bodges for Envelope
2017-01-04 Tuesday bom fix (LD1117 wrong version)
2017-01-13 Assembly data fixes, VCA revision (lm13700 pinout reversal!), Wobbler revision (better opamp scaling)
2017-02-14 Quick Master Clock Board
2017-02-25 PowerBus + EnvFollower
2017-03-09 Jig, EnvFollower, Placement
2017-05-10 MANY new board tweaks since Superbooth!
2017-05-17 Create LICENSE
2017-05-31 EnvFollower values, bigfish fixes, wobbler updates, lineout clarifications
2017-06-20 LOTS of updates..... JUNE2017 prototype sprint!
2017-09-07 Progress..
2017-09-16 Wobbler Noise Upgrades & Adding extra shifter & LEDs
2017-09-17 Wobbler reroute complete - with opamp setup made smaller.
2017-09-17 Wobbler updates.
2017-09-17 More Libs :-)
2017-09-17 Wobbler and Edgecutter progress
2017-09-17 ld components
2017-09-18 Moved TuesdayR4 to new folder, updated library components to match latest insights.
2017-09-19 Many small routing fixes & tracewidth improvements. Also split the tuesday over multiple pages.
2017-09-20 FinalEffect & AddMixShift & EspDrum
2017-09-21 BigBus - Tuesday tracenames for calibration-fixups, Finaleffect/flask routed
2017-09-22 BusUpdates
2017-09-22 frontpanel dxfs
2017-10-03 Minor tweaks pre china
2017-10-31 Perplexed, PowerBus, Wobbler/Edgecutter/Tuesday updates, FinalEffect
2017-11-09 PnP files
2017-11-11 RectangularThing! (and CEM libraries)
2017-11-12 LBR fix and rectangularthing update
2017-12-05 RectangularThing R2 & KeyboardController initial commit
2017-12-05 Stabilize pitch control in RectangularTHing
2017-12-05 Folder restructure
2017-12-05 Added Production powerstrips
2018-01-03 DelayBoard
2018-01-05 RectangularThing 2 - CEM SOIC & 36HP block
2018-01-09 RectangularThing Soics
2018-01-09 filter added..
2018-01-13 RectangularThingMovings
2018-01-24 RectangularThing progress - new suboscs, separated opamps
2018-01-27 Rectangular updates & library prefix namings
2018-02-11 Tweaks & Fixes...
2018-02-13 More tiny analog tweaks..
2018-02-19 More Boards... rectthing and keyb.
2018-02-20 Board complete - elco fixes
2018-02-23 Tweaks, Powerboard, Caps in Echochamber fixed
2018-02-24 Flask tracenames for stereo debugging
2018-03-30 RectangularThing & The Rug
2018-04-05 Backlink to CADLAB.io has been added.
2018-04-07 rectthing 3, powerbus, therug, library updates
2018-04-16 Edgecutter bodge, Ardabil, Labpower, RectangularThing & Calibrator
2018-04-20 Small Utility board to drive modules that have difficulty sharing gate/cv from the busboards.
2018-06-12 Minor tweaks...
2018-07-14 RectangularThing & Fresiaboard
2018-08-14 RectangularThing production tweaks, Wobbler descriptors.
2018-08-15 Alternative frontpanel for Tuesday - designed by Endurance!
2018-08-15 previews
2018-08-17 Ardabil progress
2019-02-23 error smd mounts, library updates
2019-03-31 Small tweaks to library parts.
2019-05-31 Nein & Ardabil
2019-06-30 Ardabil update
2019-09-13 some production files
2019-09-13 production files
2019-09-17 jackdemo thingie
2019-09-20 Opl update
2019-10-21 Modules update
2019-10-21 AllOfTheAbove
2019-10-21 9pwr - opamp - testpad
2019-10-23 Dist+ added
2019-10-23 Some fixes to keep 7.7 compat
2019-10-24 Rat added with powerjumpers
2019-10-24 Commit fix
2019-10-25 Added FF&Muff schematic (.brd not updated)
2019-10-29 VCA added
2019-10-29 Updated Values
2019-10-29 5 Stompboard & library part
2019-10-30 Demoboard en Keyboard
2019-10-31 Keyboard stuff, Stompstuff, bubbles!
2019-11-04 VCA+Crossfader+Envelope+Inputs
2019-11-04 Lots of edits!
2019-11-04 Boardstuff
2019-11-04 Design file, dxf file
2019-11-04 moving stuff... POW
2019-11-05 Consistency
2019-11-05 Updated Schematic/Fixed ICs etc
    Pak de 5nov versie voor de laatste 7x!
2019-11-05 Design dingen
2019-11-05 Board edited
2019-11-05 FrontPush, keyboard model
2019-11-05 position fixes
2019-11-05 Updated board
2019-11-05 board and sch
2019-11-05 vs stuff
2019-11-06 design tweaks
2019-11-09 keyboard design
2019-11-09 Kein beetje aan het board gezeten
2019-11-11 Teensykeyboard..
2019-11-12 Finished Board placements
2019-11-12 TeensyKeyboard
2019-11-12 Pushpush
2019-11-12 12novvers
2019-11-13 Boardedits
2019-11-14 Meer boardstate
2019-11-14 Some routing, output E fix
2019-11-14 1 more fix
2019-11-15 Lijntjes trekken
2019-11-16 design tweaks - keyboard ino file
2019-11-16 16nov = Laatste versie
2019-11-17 ROUTING KLAAR
    Eindelijk
2019-11-18 Navenant.
2019-11-20 Opinionated!
2019-11-20 overstuur
2019-11-21 Speaker order - Simplekeyboard TRS midi - Overstuur design
2019-11-25 Teensy Quantize Test
2019-11-26 updates stm/quant
2019-11-27 Some stuff..
2019-11-27 board control
2019-11-27 cvouts done
2019-11-28 meer stuff aan de plank
2019-12-02 SwitchTester
2019-12-02 Switchtest update
2019-12-03 more edits to board
2019-12-03 nieuwste board!
2019-12-03 Reordered miniled pins.. and added minikeyboard
2019-12-04 Chips neergezet
2019-12-04 Added final components?
2019-12-04 board en schema sync
2019-12-04 powertesters onderin
2019-12-04 power updated
2019-12-05 extra routing... 5v voor usb
2019-12-07 board af
2019-12-09 nieuw board stm
2019-12-10 boardupdates
2019-12-12 Added Boards as Ordered before fixes
2019-12-12 nieuwe versie OVERSTUUR
2019-12-14 92 airwires to go!
2019-12-15 beetje routing
2019-12-16 bijna klaar.jpg
2019-12-16 99.9% klaar
2019-12-16 STM32 KLAAR
2019-12-16 Unsmash labels, cam export
2019-12-16 frontpanel
2019-12-16 afdesign
2019-12-19 Minikeyb, STM32
2019-12-22 Pre-ARcomp gate update
2019-12-29 AR envelope gate
2019-12-30 arboard los
2020-01-03 ARboard shenanigans
2020-02-07 Summing mixer - envelope_out link
2020-02-17 more wrong trace cleanup
2020-02-18 Update Overstuur Board
2020-02-27 RectangularThing LEDboard v1
2020-03-02 Jac Powerboard
2020-03-03 Layer Visibility for minikeyb
2020-03-06 Some overstuur resistors
2020-03-13 CNC board
2020-03-14 CNCDriver
2020-03-16 tiny overstuur schematic fixes
2020-03-24 Westlaunch as ordered
2020-04-04 Westlaunch - esp32 clap
2020-06-15 bunch of experiments + pjb things added
2020-06-15 Tunneldiode!
2020-06-25 PJB Mainboard, OPL fixes, teensyparts, powerbackpack
2020-07-10 bunch of pjb boards - tentative mixer design..
2020-07-13 simplemixer setup... not serious yet
2020-09-17 Some new boards..
2020-10-08 Bunch of stuff again..
2020-10-21 Some rotation standardization
2020-11-10 SWD isolator -pjb board progress
2020-11-24 some code and opl lib updates
2020-12-15 isolator tweaks, lbr updates
2020-12-21 zephcomponents
2020-12-21 FishStandoffs
2021-06-21 progress in the lineup..
2021-07-01 wobbler2 progress - some space
2021-07-03 wobbler and switch progress
2021-07-05 Wobbler ordered.. picolooper?
2021-07-06 looper and stuff
2021-07-08 looper...
2021-07-10 looper orderable, wobbler adjustments, fenixcase power board
2021-07-27 some board updates..
2021-07-27 Loopercode update
2021-07-27 looper things and wobbler2drum base
2021-07-28 reset position to 0 on the next clock when pressing start.
2021-07-29 more looping and wobbling
2021-09-22 Minor Updates..
2022-02-11 Update .gitignore
    ignore update
2022-02-11 Space In Kicad
2022-02-11 c&o
    criminally ornamental
2022-02-11 Space..
2022-02-23 wobbler2 and space kicad stuff
2022-02-26 Wobbler2 routed?
2022-02-27 Wobbler2 kicad
2022-03-01 wobbler2 code & sim initial
2022-03-01 wobbler2 stuff
2022-03-01 Makelists
2022-03-01 kicad touches weird files
2022-03-01 mac/windows both work now!
2022-03-03 Wobbler2 sim
2022-03-03 Wobbler2 sim includes.
2022-03-03 libfixmath ref
2022-03-04 Wobbler2 Druminstances in simulator - pattern playback
2022-03-07 Wobbler Sim Progress
2022-03-08 Wobbler2 Drummings
2022-03-17 More drumming
2022-04-01 drumming
2022-06-04 Wobbler2 Kicad Version
2022-06-04 Lots of backlog crap
